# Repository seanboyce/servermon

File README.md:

# An ESP8266-based Server Monitor
This ESP8266-based server monitor PCB displays the status of up to 8 servers with RGB LEDs. If it receives HTTP 200, the LED will turn green. If it receives anything else, it will turn yellow the first time and red subsequent times.

The big white patches of silkscreen are there for you to write the server names on. You can use whiteboard markers if they change often, permanent marker (clean off with ethanol) or labels.

The firmware is just an Arduino sketch. I've done it this way because Arduino is popular, so this is the easiest for most people to modify.

It will send the HTTP GET requests with https, but will not verify the certificates. This is by design -- there's not much memory on an ESP8266, and you'd have to go through the hassle of loading the certificates onto the MCU storage manually. This is also why it only sends one request at a time instead of creating a http client and then sending all 9. That would often causes out-of-memory errors!

# BOM
- 1x ESP8266 mini-D1 pro. The non-pro version will work, but you'll have to solder in header pins, then solder those directly the pads on the board. The Pro version is lower profile and solders flush to the board. 
- 1x TM1640 LED driver
- 8x 5050 RGB LED
- 1x 1411 Tantalum capacitor 100uf 6.3V (you can use electrolytic but it will be bigger)
- 1x 0603 0.1uF ceramic capacitor 50V
- 4x 0402 10k ohm resistor
- 1x 0402 20k ohm resistor (this is for the power LED to make it similar brightness to the others. If you don't care, you can use another 10k)
- 3x 0603 red LED (or any color that works under ESP8266 GPIO HIGH voltage)
- Antenna for mini-D1 Pro (optional)
- 1x PCB

# Total Cost

In Asia, about VND 164.550 ($6.31) without antenna or 190.000 (7.29) with antenna (board included, assuming you make 5 units). In the West probably double, but it's still pretty cheap!

# Photo

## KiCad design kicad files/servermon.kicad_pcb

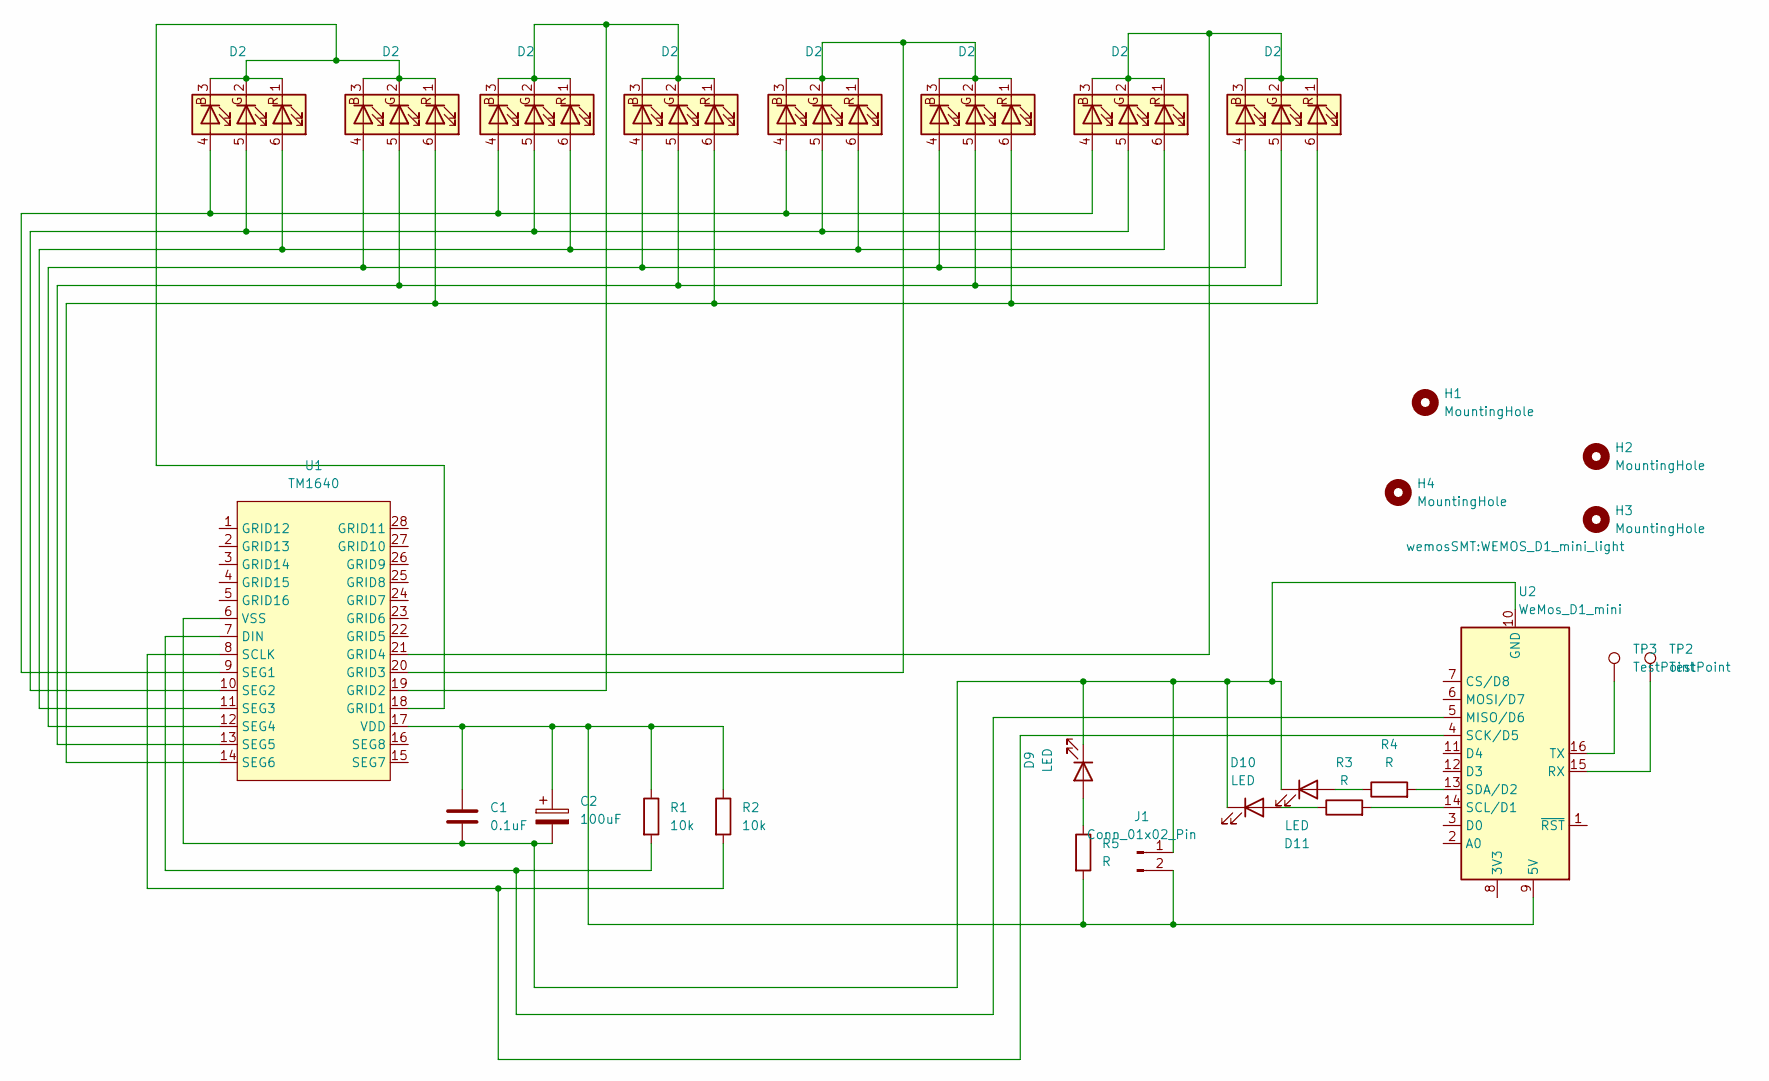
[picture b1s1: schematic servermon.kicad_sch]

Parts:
C1: 0.1uF; C_0603_1608Metric
C2: 100uF; CP_EIA-3528-12_Kemet-T
D1, D2, D3, D4, D5, D6, D7, D8: D2; LED_RGB_5050-6
D9, D10, D11: LED; LED_0603_1608Metric
H1, H2, H3, H4: MountingHole; MountingHole_3.2mm_M3
J1: Conn_01x02_Pin; JST_EH_B2B-EH-A_1x02_P2.50mm_Vertical
R1, R2: 10k; R_0402_1005Metric
R3, R4, R5: R; R_0402_1005Metric
TP2, TP3: TestPoint; TestPoint_Pad_D2.0mm
U1: TM1640
U2: WeMos_D1_mini; WEMOS_D1_mini_light

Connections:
unnamed: D1.4 (BA), D3.4 (BA), D5.4 (BA), D7.4 (BA), U1.9 (SEG1)
unnamed: D1.1 (RK), D1.2 (GK), D1.3 (BK), D2.1 (RK), D2.2 (GK), D2.3 (BK), U1.18 (GRID1)
unnamed: D1.5 (GA), D3.5 (GA), D5.5 (GA), D7.5 (GA), U1.10 (SEG2)
unnamed: D1.6 (RA), D3.6 (RA), D5.6 (RA), D7.6 (RA), U1.11 (SEG3)
unnamed: D2.4 (BA), D4.4 (BA), D6.4 (BA), D8.4 (BA), U1.12 (SEG4)
unnamed: D2.5 (GA), D4.5 (GA), D6.5 (GA), D8.5 (GA), U1.13 (SEG5)
unnamed: D2.6 (RA), D4.6 (RA), D6.6 (RA), D8.6 (RA), U1.14 (SEG6)
unnamed: D3.1 (RK), D3.2 (GK), D3.3 (BK), D4.1 (RK), D4.2 (GK), D4.3 (BK), U1.19 (GRID2)
unnamed: D5.1 (RK), D5.2 (GK), D5.3 (BK), D6.1 (RK), D6.2 (GK), D6.3 (BK), U1.20 (GRID3)
unnamed: D7.1 (RK), D7.2 (GK), D7.3 (BK), D8.1 (RK), D8.2 (GK), D8.3 (BK), U1.21 (GRID4)
unnamed: D9.2 (A), R5.1
unnamed: D10.2 (A), R3.1
unnamed: C1.2, C2.2, D9.1 (K), D10.1 (K), D11.1 (K), J1.1, U1.6 (VSS), U2.10 (GND)
unnamed: D11.2 (A), R4.1
unnamed: C1.1, C2.1, J1.2, R1.1, R2.1, R5.2, U1.17 (VDD), U2.9 (5V)
unnamed: R1.2, U1.7 (DIN), U2.5 (MISO/D6)
unnamed: R2.2, U1.8 (SCLK), U2.4 (SCK/D5)
unnamed: TP2.1, U2.15 (RX)
unnamed: R3.2, U2.14 (SCL/D1)
unnamed: R4.2, U2.13 (SDA/D2)
unnamed: TP3.1, U2.16 (TX)

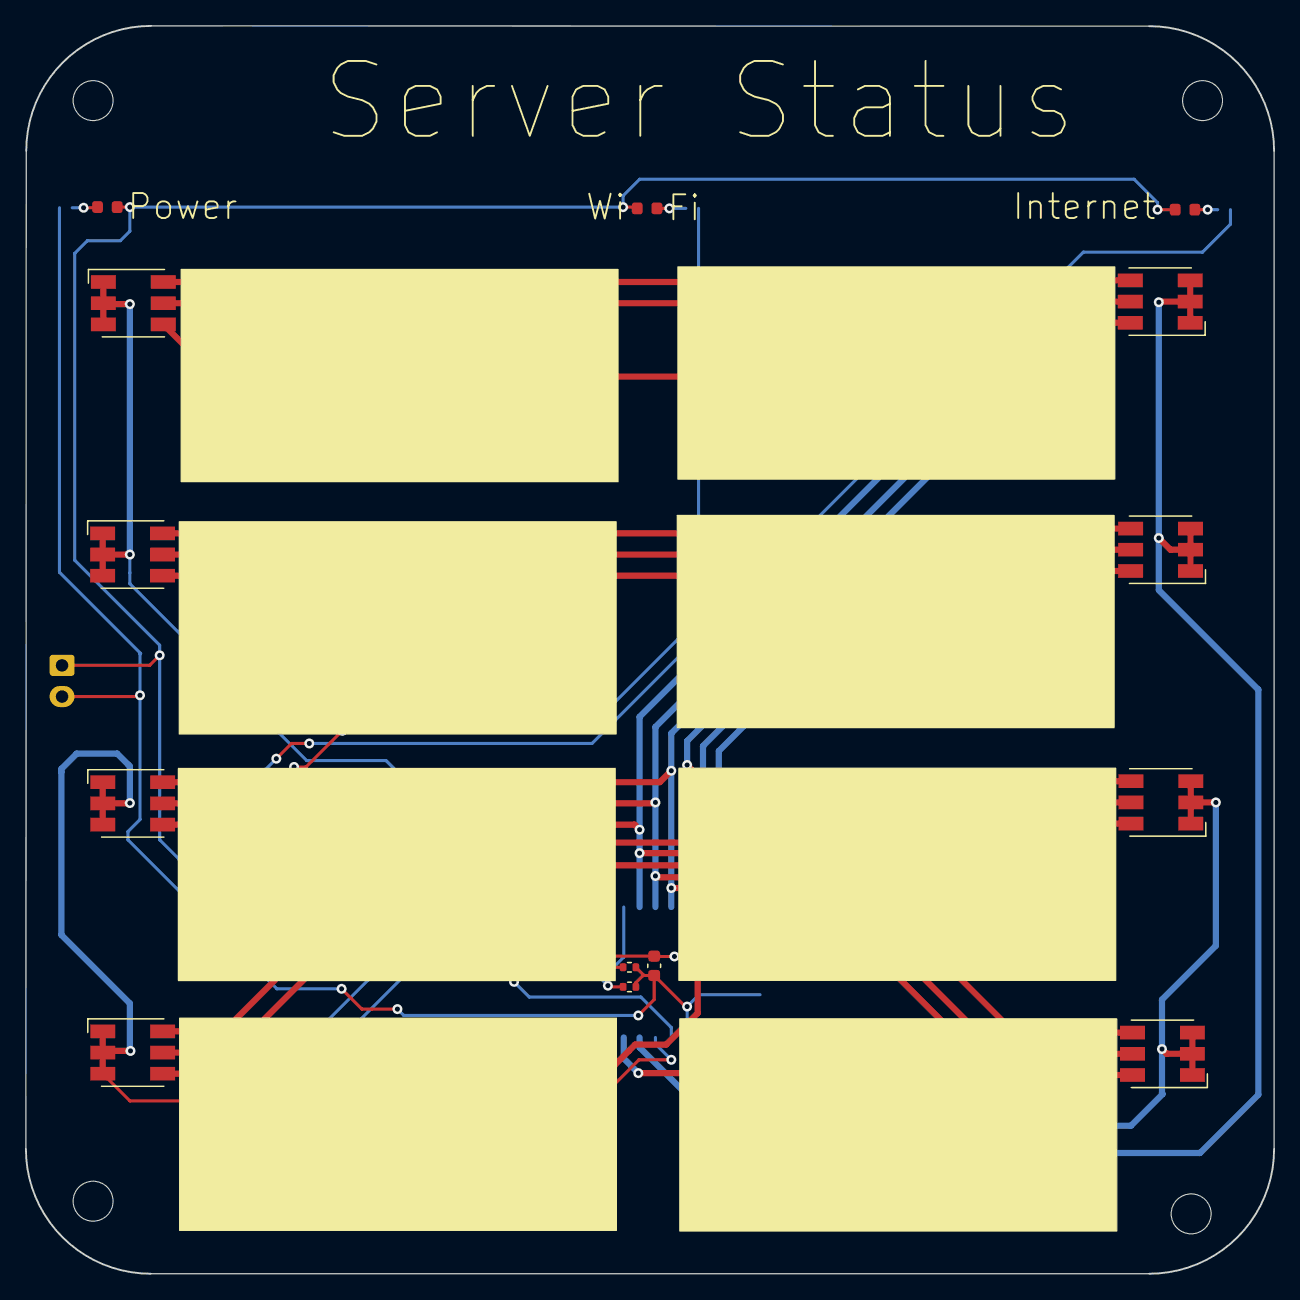
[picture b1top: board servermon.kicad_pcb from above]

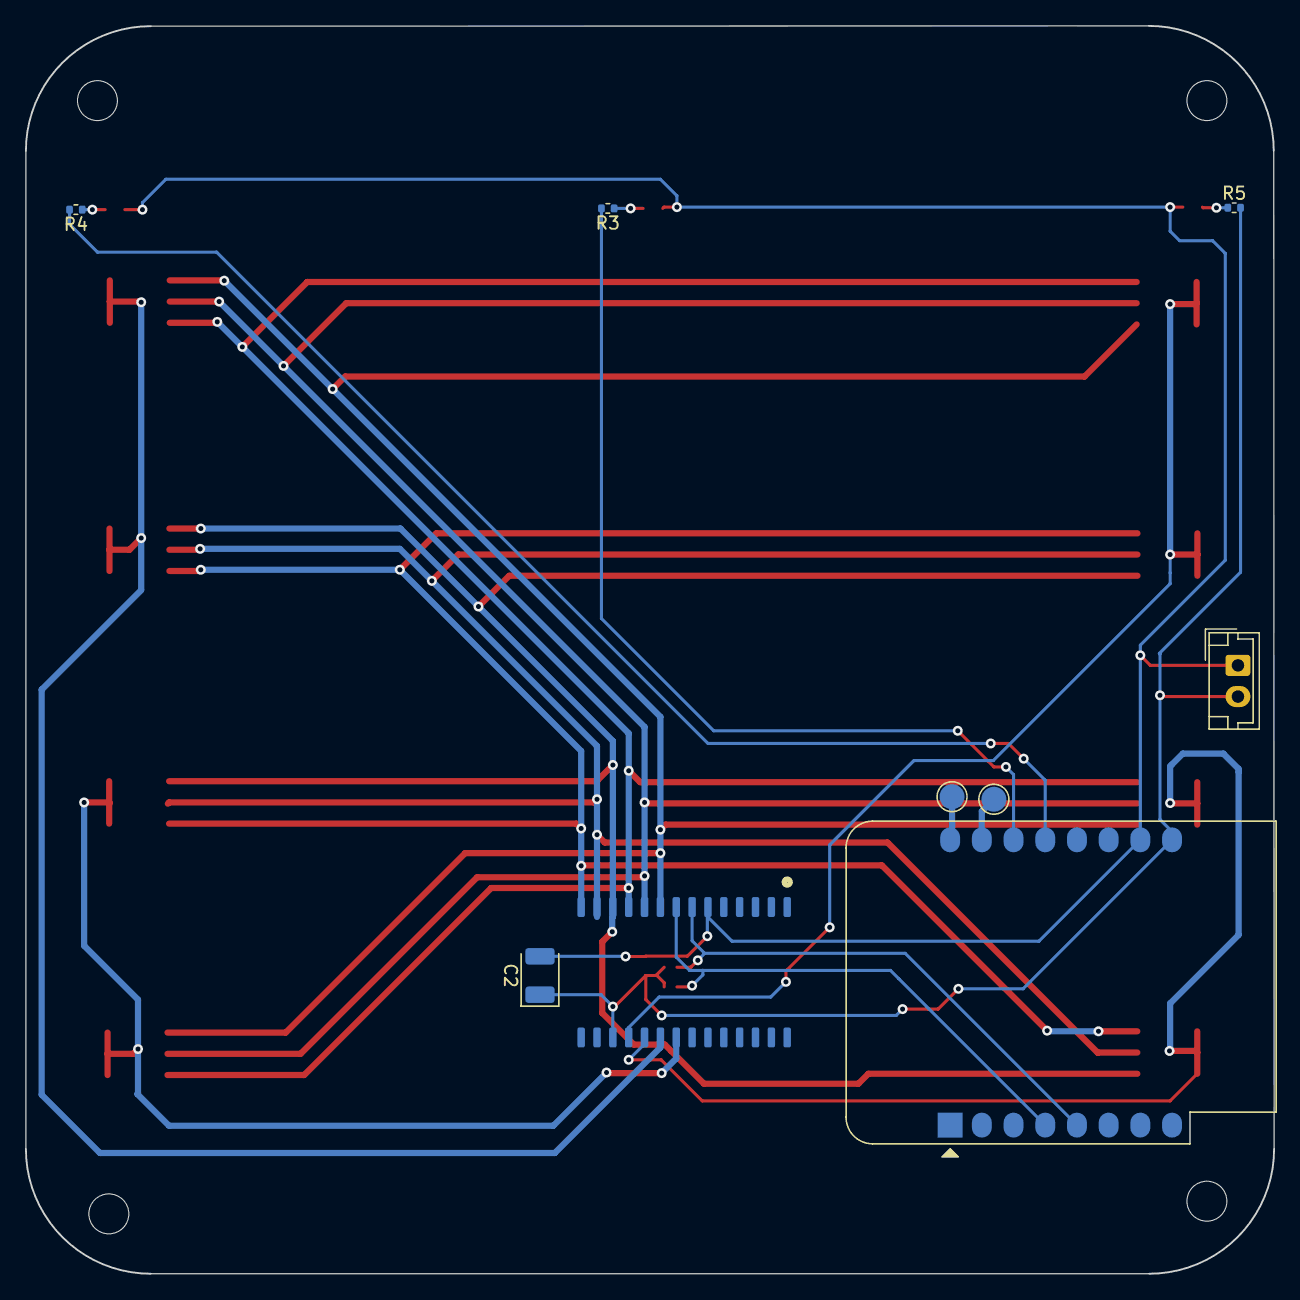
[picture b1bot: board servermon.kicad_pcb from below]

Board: 2 copper layers, 100.0 x 100.0 mm, 27 parts (9 on the bottom side), 21 nets.

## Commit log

2025-06-15 Add files via upload
    Add KiCAD and production files for the PCB.
2025-06-15 Update README.md
    Add description, BOM, Cost
2025-06-15 Add firmware
2025-06-15 Add files via upload
    Add image
2025-06-15 Create LICENSE
